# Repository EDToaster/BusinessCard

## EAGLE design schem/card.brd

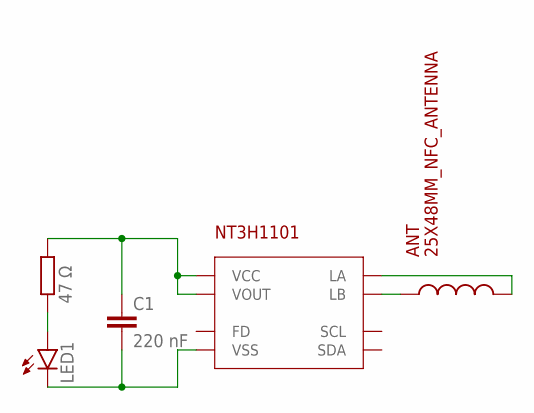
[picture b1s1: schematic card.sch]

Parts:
ANT: 25X48MM_NFC_ANTENNA
C1: 220 nF; C0603
LED1: LEDCHIP-LED0603; CHIP-LED0603
NT3H1101: NT3H; XQFN8
R1: 47 Ω; R0603

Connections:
unnamed: ANT.P$1, NT3H1101.LB
unnamed: ANT.P$2, NT3H1101.LA
unnamed: LED1.A, R1.1
unnamed: C1.1, NT3H1101.VCC, NT3H1101.VOUT, R1.2
unnamed: C1.2, LED1.C, NT3H1101.VSS

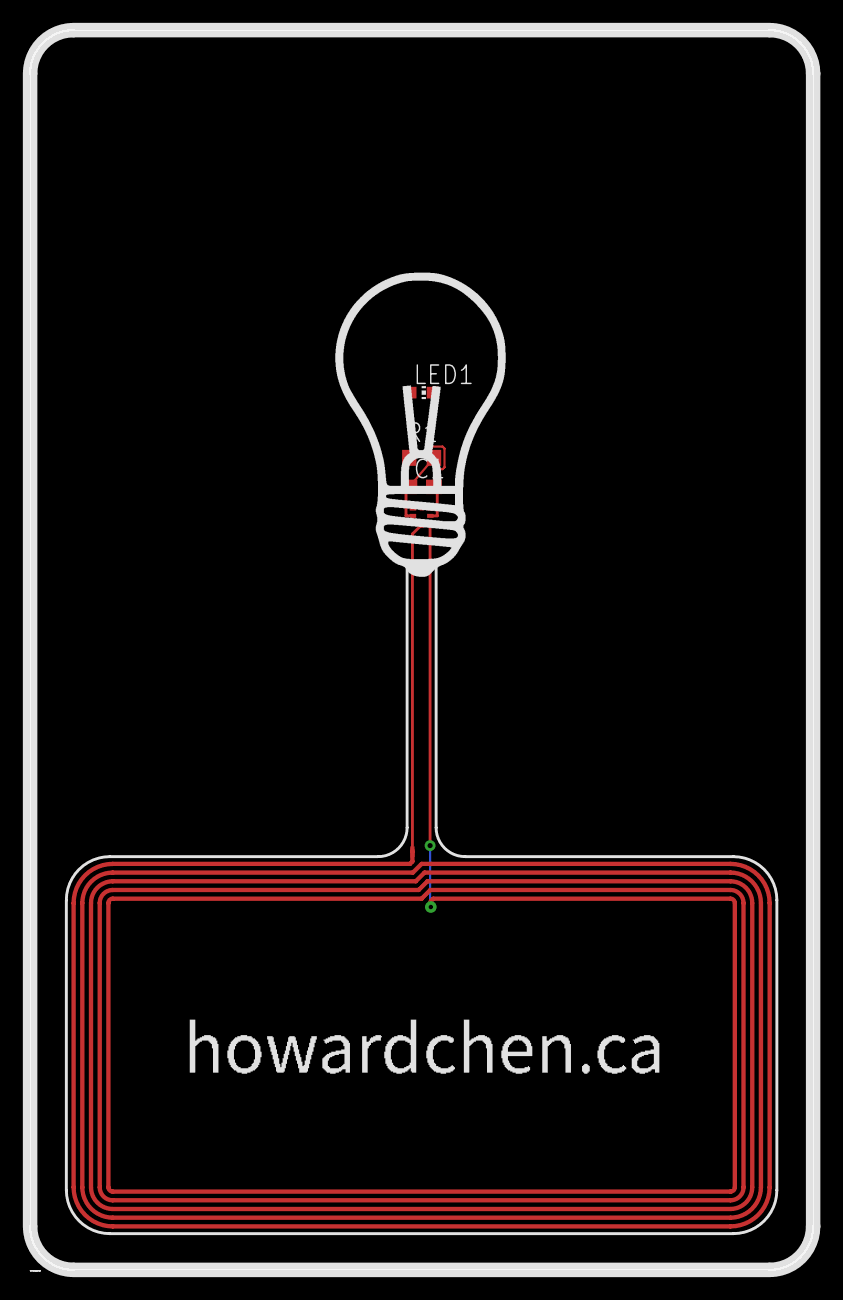
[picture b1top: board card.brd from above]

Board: 2 copper layers, 54.0 x 85.5 mm, 5 parts (0 on the bottom side), 5 nets.

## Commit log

2020-02-17 Added schem files
